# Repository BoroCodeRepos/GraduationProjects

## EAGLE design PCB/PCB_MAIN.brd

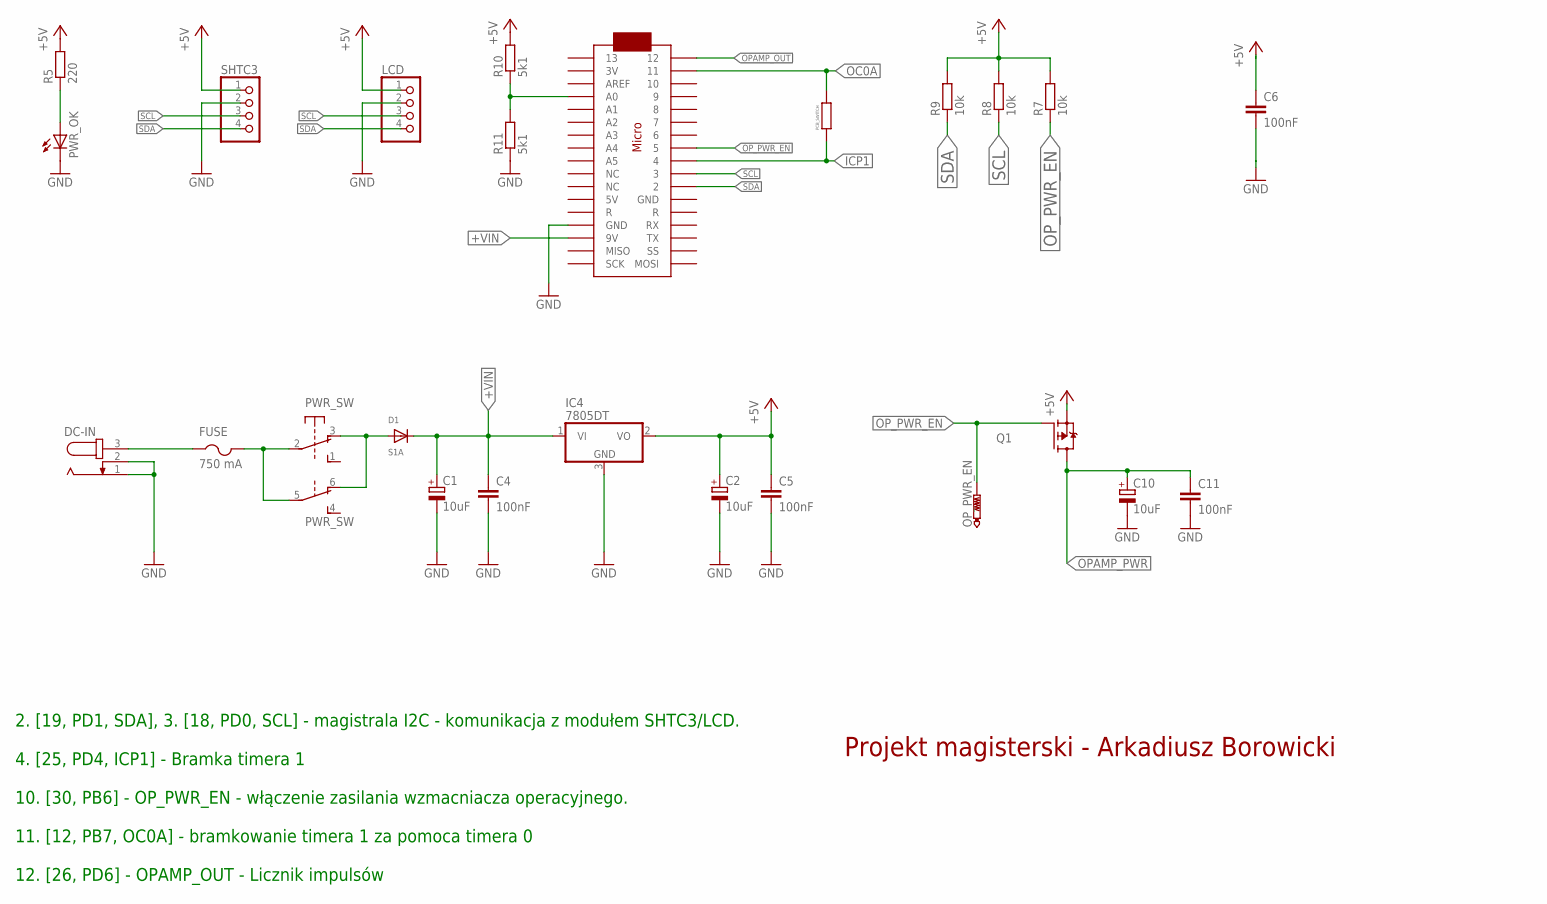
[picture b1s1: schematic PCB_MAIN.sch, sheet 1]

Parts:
C1, C2, C10: 10uF; 153CLV-0605
C4, C5, C6, C11: 100nF; C1206K
D1: S1A; SMADIODE
DC-IN: JACK-PLUG1; SPC4078
FUSE: 750 mA; 1812
IC4: 7805DT; TO252
LCD: PINHD-1X4; 1X04
OP_PWR_EN: PTR1TP20R; TP20R
PCB_SWITCH: R-EU_R0402; R0402
PWR_OK: LEDSMT1206; 1206
PWR_SW: 9077-2
Q1: SPD30P06PTO252; TO252
R5: 220; R1206
R7, R8, R9: 10k; R1206
R10, R11: 5k1; R1206
SHTC3: PINHD-1X4; 1X04
U$1: ARDUINOMICRO

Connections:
+5V: C2.+, C5.1, C6.1, IC4.2 (VO), LCD.1, Q1.2 (S), R5.2, R7.2, R8.2, R9.2, R10.2, SHTC3.1; also elsewhere on the board
+VIN: C1.+, C4.1, D1.C, IC4.1 (VI), U$1.P$20 (9V)
GND: C1.-, C2.-, C4.2, C5.2, C6.2, C10.-, C11.2, DC-IN.1, DC-IN.2, IC4.3 (GND), LCD.2, PWR_OK.C, R11.1, SHTC3.2, U$1.P$12 (GND); also elsewhere on the board
ICP1: PCB_SWITCH.1, U$1.P$9 (4)
unnamed: R10.1, R11.2, U$1.P$31 (A0)
unnamed: DC-IN.3, FUSE.1
unnamed: PWR_OK.A, R5.1
unnamed: D1.A, PWR_SW.3 (O), PWR_SW.6 (O)
unnamed: FUSE.2, PWR_SW.2, PWR_SW.5
OC0A: PCB_SWITCH.2, U$1.P$2 (11)
OPAMP_OUT: U$1.P$1 (12); also elsewhere on the board
OPAMP_PWR: C10.+, C11.1, Q1.3 (D); also elsewhere on the board
OP_PWR_EN: OP_PWR_EN.TP, Q1.1 (G), R7.1, U$1.P$8 (5)
SCL: LCD.3, R8.1, SHTC3.3, U$1.P$10 (3)
SDA: LCD.4, R9.1, SHTC3.4, U$1.P$11 (2)

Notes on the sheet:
2. [19, PD1, SDA], 3. [18, PD0, SCL] - magistrala I2C - komunikacja z modułem SHTC3/LCD. 4. [25, PD4, ICP1] - Bramka timera 1 10. [30, PB6] - OP_PWR_EN - włączenie zasilania wzmacniacza operacyjnego. 11. [12, PB7, OC0A] - bramkowanie timera 1 za pomoca timera 0 12. [26, PD6] - OPAMP_OUT - Licznik i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
Projekt magisterski - Arkadiusz Borowicki

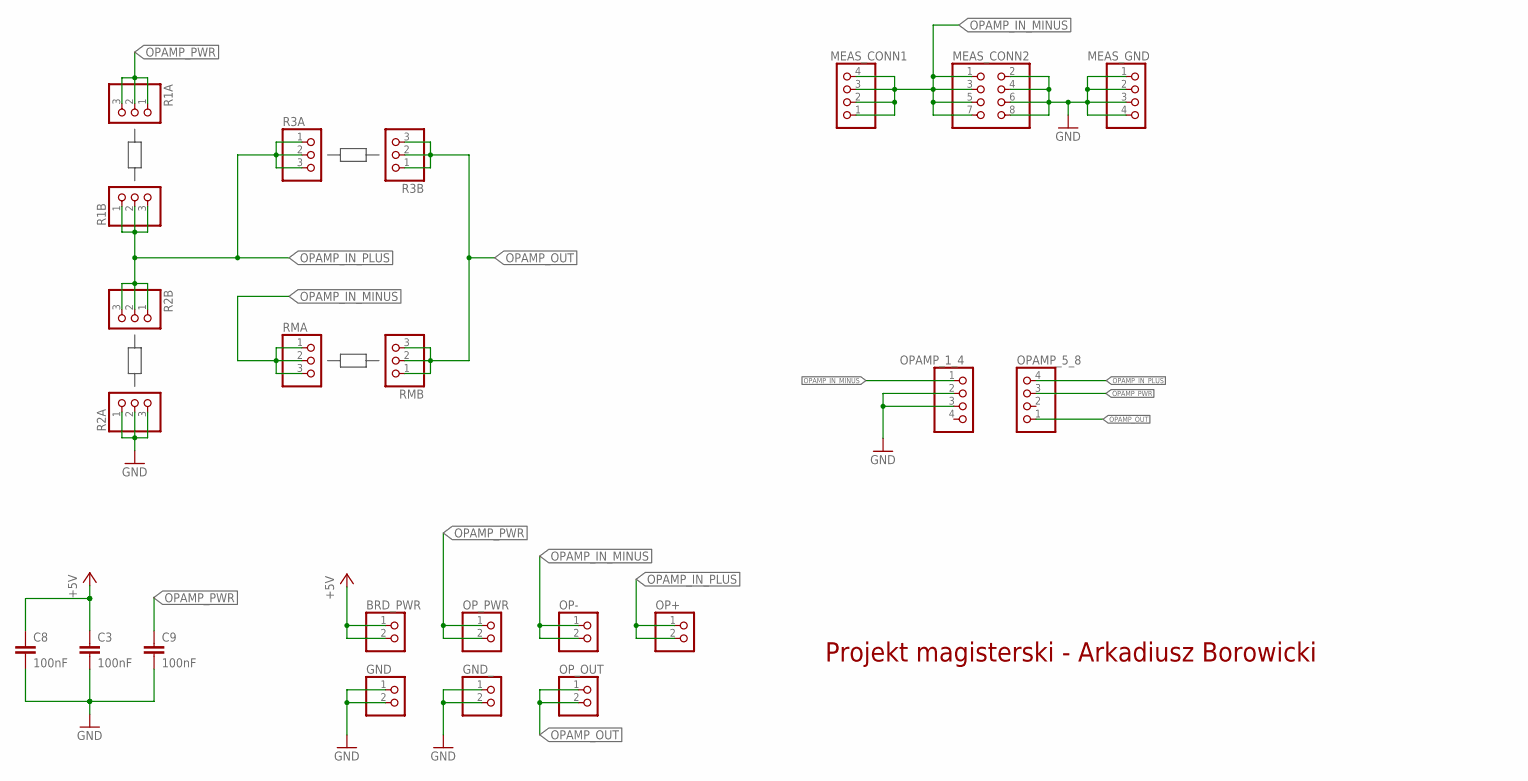
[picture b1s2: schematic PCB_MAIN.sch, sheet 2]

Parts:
BRD_PWR: PINHD-1X2; 1X02
C3, C8, C9: 100nF; C1206K
GND: PINHD-1X2; 1X02
GND_: PINHD-1X2; 1X02
MEAS_CONN1: PINHD-1X4; 1X04
MEAS_CONN2: PINHD-2X4; 2X04
MEAS_GND: PINHD-1X4; 1X04
OP+: PINHD-1X2; 1X02
OP-: PINHD-1X2; 1X02
OPAMP_1_4, OPAMP_5_8: PINHD-1X4; 1X04
OP_OUT: PINHD-1X2; 1X02
OP_PWR: PINHD-1X2; 1X02
R1A, R1B, R2A, R2B, R3A, R3B: PINHD-1X3; 1X03
RMA: PINHD-1X3; 1X03
RMB: PINHD-1X3; 1X03

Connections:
+5V: BRD_PWR.1, BRD_PWR.2, C3.1, C8.1; also elsewhere on the board
GND: C3.2, C8.2, C9.2, GND.1, GND.2, GND_.1, GND_.2, MEAS_CONN2.2, MEAS_CONN2.4, MEAS_CONN2.6, MEAS_CONN2.8, MEAS_GND.1, MEAS_GND.2, MEAS_GND.3, MEAS_GND.4, OPAMP_1_4.2, OPAMP_1_4.3, R2A.1, R2A.2, R2A.3; also elsewhere on the board
OPAMP_IN_MINUS: MEAS_CONN1.1, MEAS_CONN1.2, MEAS_CONN1.3, MEAS_CONN1.4, MEAS_CONN2.1, MEAS_CONN2.3, MEAS_CONN2.5, MEAS_CONN2.7, OP-.1, OP-.2, OPAMP_1_4.1, RMA.1, RMA.2, RMA.3
OPAMP_IN_PLUS: OP+.1, OP+.2, OPAMP_5_8.4, R1B.1, R1B.2, R1B.3, R2B.1, R2B.2, R2B.3, R3A.1, R3A.2, R3A.3
OPAMP_OUT: OPAMP_5_8.1, OP_OUT.1, OP_OUT.2, R3B.1, R3B.2, R3B.3, RMB.1, RMB.2, RMB.3; also elsewhere on the board
OPAMP_PWR: C9.1, OPAMP_5_8.3, OP_PWR.1, OP_PWR.2, R1A.1, R1A.2, R1A.3; also elsewhere on the board

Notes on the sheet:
Projekt magisterski - Arkadiusz Borowicki

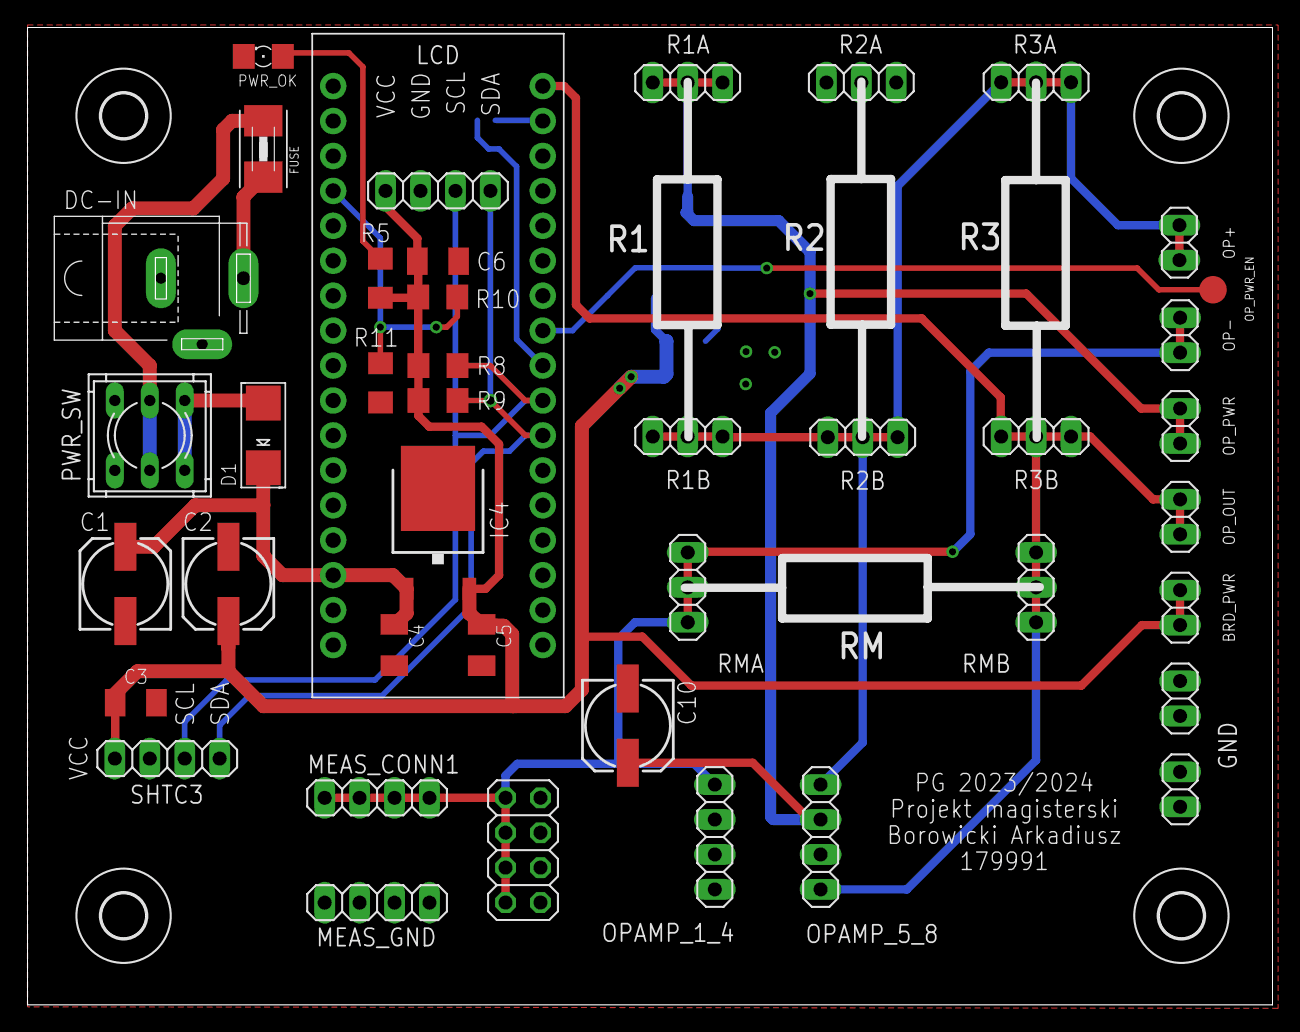
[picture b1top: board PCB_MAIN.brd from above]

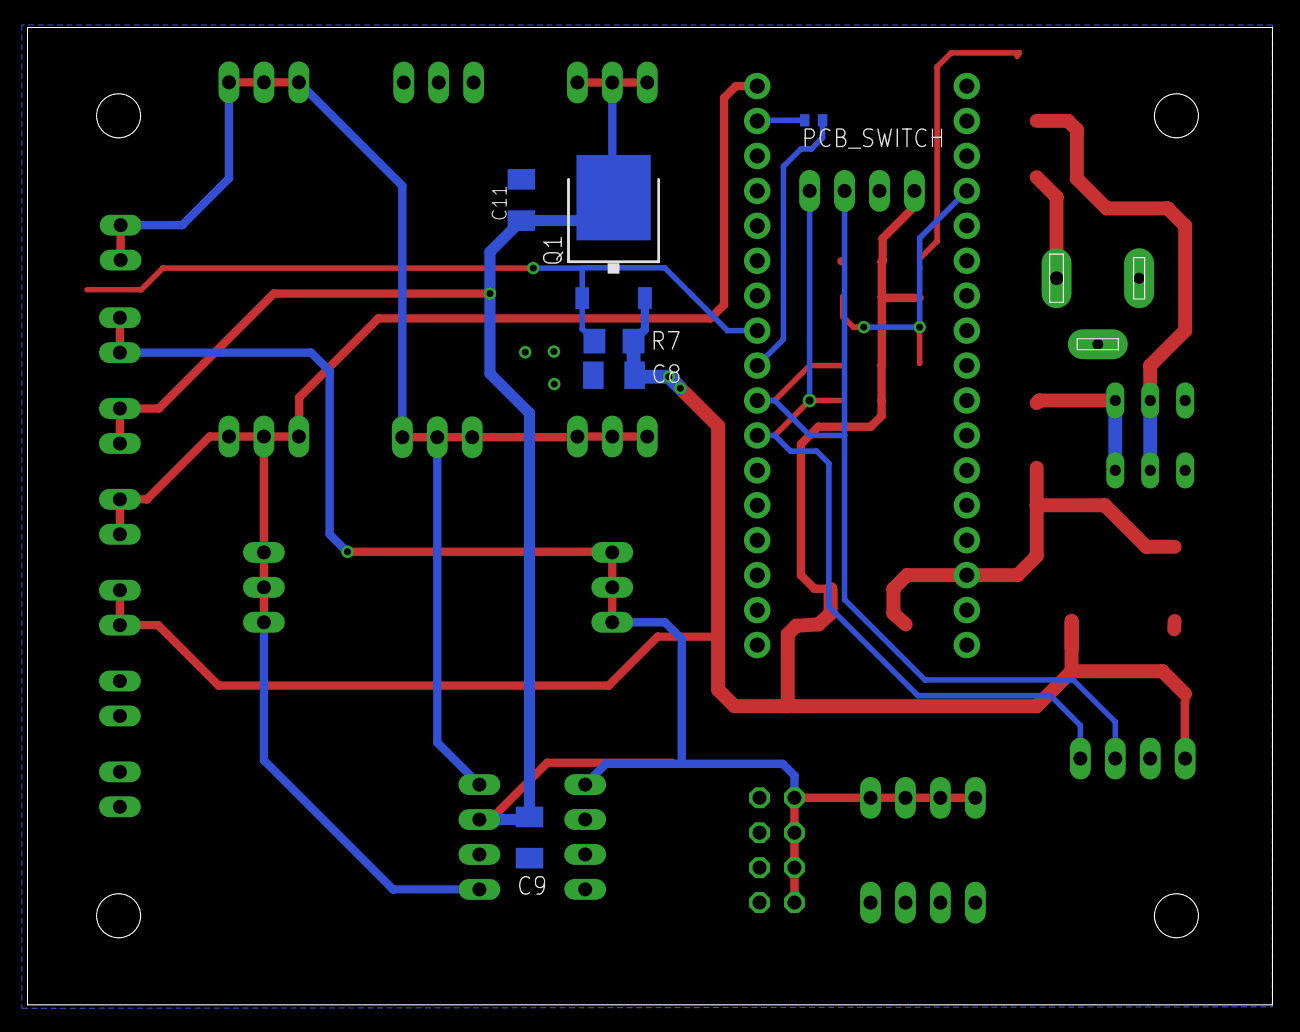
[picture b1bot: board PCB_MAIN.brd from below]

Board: 2 copper layers, 90.5 x 71.1 mm, 52 parts (6 on the bottom side), 17 nets.

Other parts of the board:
U$2, U$3, U$4, U$5: 3,2

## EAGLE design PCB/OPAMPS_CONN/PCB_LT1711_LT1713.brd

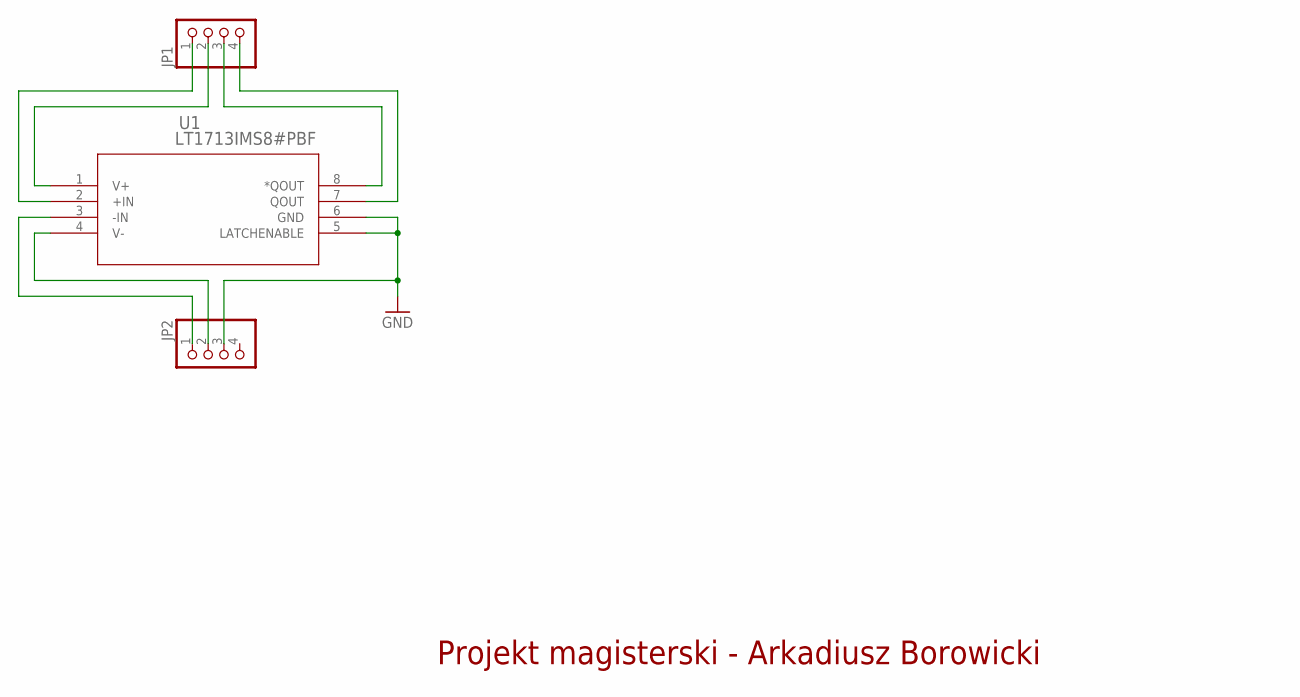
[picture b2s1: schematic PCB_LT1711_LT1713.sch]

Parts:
JP1, JP2: PINHD-1X4; 1X04
U1: LT1713IMS8#PBF; MSOP-8_MS

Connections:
GND: JP2.3, U1.5 (LATCHENABLE), U1.6 (GND)
unnamed: JP1.2, U1.1 (V+)
unnamed: JP1.1, U1.2 (+IN)
unnamed: JP2.1, U1.3 (-IN)
unnamed: JP2.2, U1.4 (V-)
unnamed: JP1.3, U1.8 (*QOUT)
unnamed: JP1.4, U1.7 (QOUT)

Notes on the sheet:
Projekt magisterski - Arkadiusz Borowicki

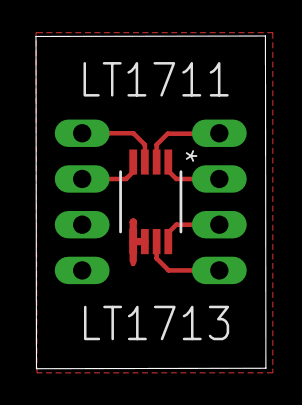
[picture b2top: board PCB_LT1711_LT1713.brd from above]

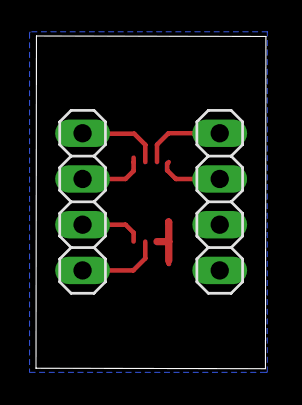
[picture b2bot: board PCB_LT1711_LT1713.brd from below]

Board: 2 copper layers, 12.8 x 18.5 mm, 3 parts (2 on the bottom side), 7 nets.

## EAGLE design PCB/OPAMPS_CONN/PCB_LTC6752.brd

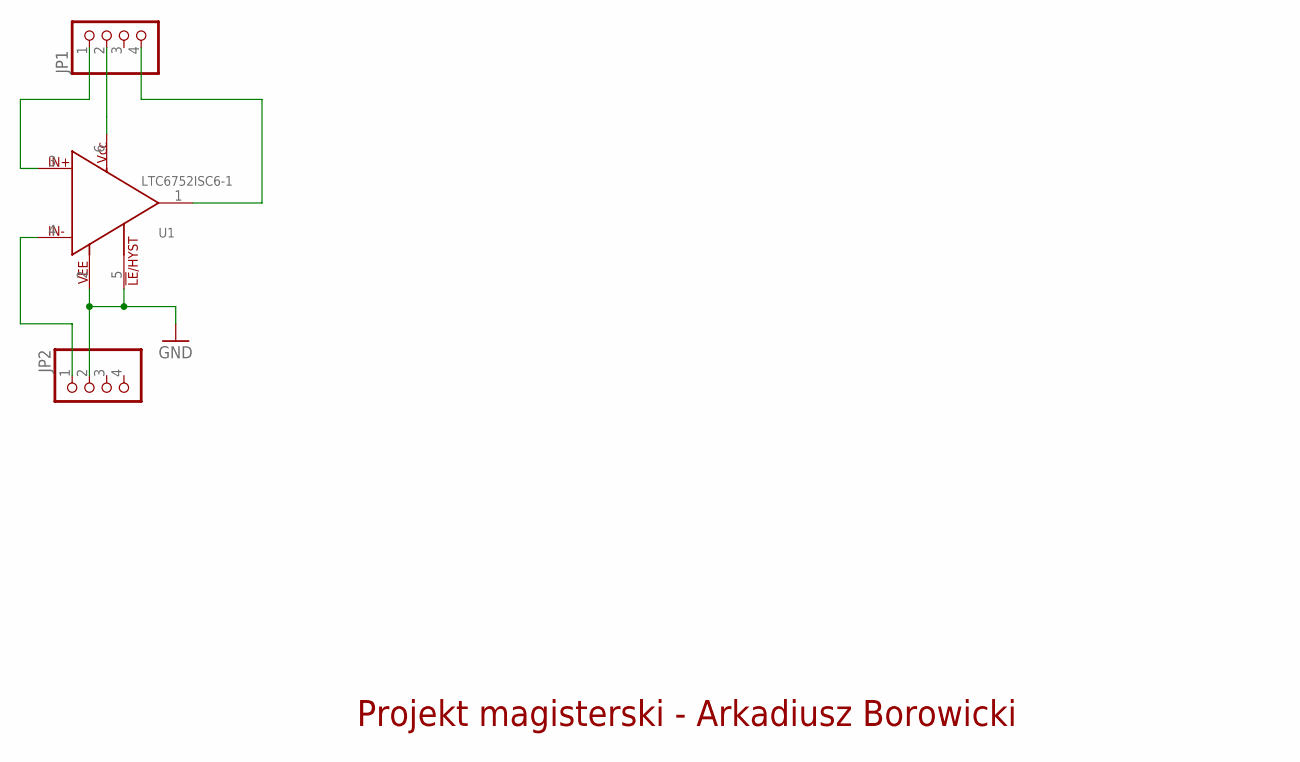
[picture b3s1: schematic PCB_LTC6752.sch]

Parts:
JP1, JP2: PINHD-1X4; 1X04
U1: LTC6752ISC6-1; SC70-6

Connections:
GND: JP2.2, U1.2 (VEE), U1.5 (HYST)
unnamed: JP1.2, U1.6 (VCC)
unnamed: JP1.1, U1.3 (IN+)
unnamed: JP2.1, U1.4 (IN-)
unnamed: JP1.4, U1.1 (OUT)

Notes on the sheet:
Projekt magisterski - Arkadiusz Borowicki

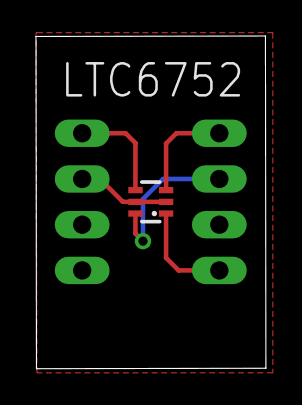
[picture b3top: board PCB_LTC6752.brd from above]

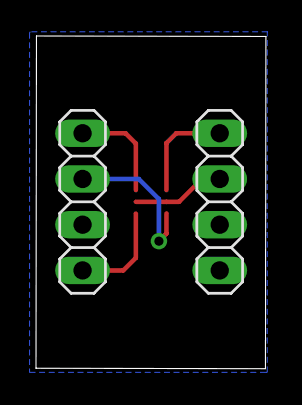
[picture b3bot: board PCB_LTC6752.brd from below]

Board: 2 copper layers, 12.8 x 18.5 mm, 3 parts (2 on the bottom side), 5 nets.

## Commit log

2022-09-26 Praca Inżynierska v.1
2022-10-09 Aktualizacja programu desktopowego i skryptów matlabowych
2022-10-11 Praca nad rozdziałem 3
2022-11-06 Praca nad dokumentem
2022-11-06 Aktualizacja programów
2022-11-06 Dopracowanie interfejsu użytkownika
2022-11-15 Praca nad dokumentem roz. 8
2022-11-16 Wstep i zakonczenie
2022-11-17 Zakonczenie - przekazanie do akceptacji
2022-12-09 Ostatnie poprawki
2022-12-15 Oddanie do recenzji
2024-09-16 Praca magisterka.
